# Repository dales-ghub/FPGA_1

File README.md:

A simple FPGA design using a Lattice ICE40UP5K. Does not have memory and is intended to be programmed exernally. Takes 3V3 volts on pin 40 and has regulator for 1V2.

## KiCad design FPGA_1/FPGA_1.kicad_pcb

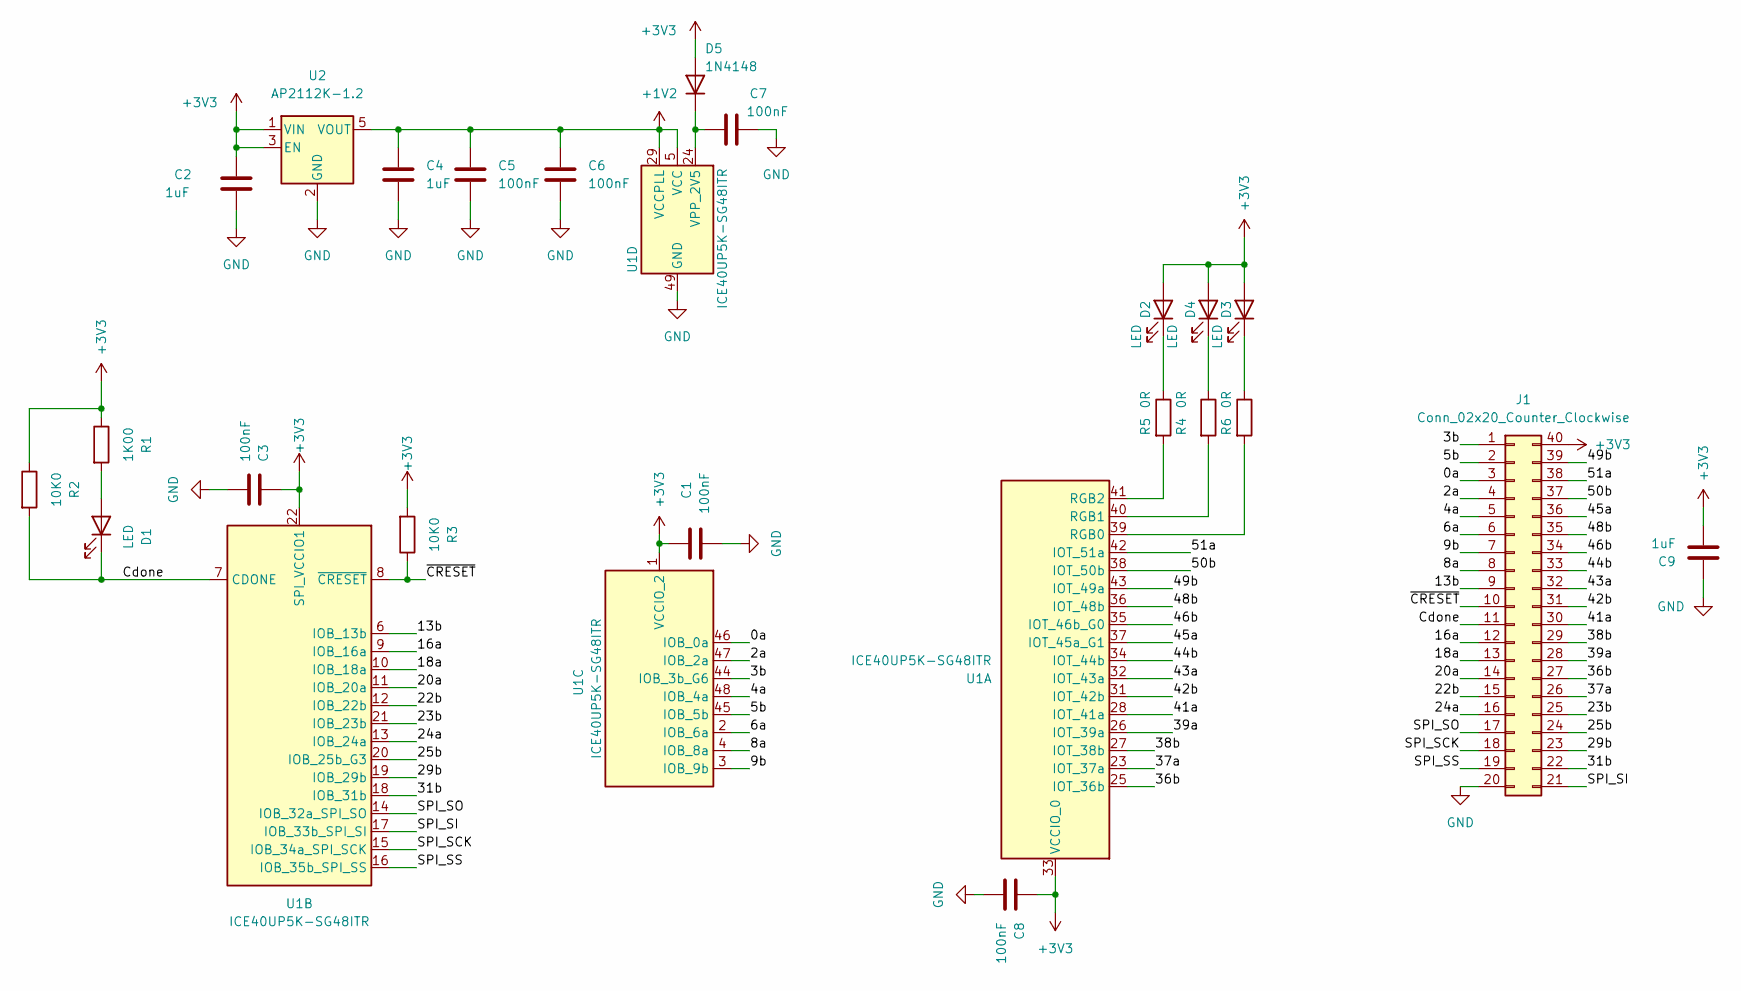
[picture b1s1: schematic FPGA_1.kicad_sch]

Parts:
C1, C3, C5, C6, C7, C8: 100nF; C_0402_1005Metric_Pad0.74x0.62mm_HandSolder
C2, C4, C9: 1uF; C_0402_1005Metric_Pad0.74x0.62mm_HandSolder
D1, D2, D3, D4: LED; LED_0603_1608Metric
D5: 1N4148; D_0402_1005Metric_Pad0.77x0.64mm_HandSolder
J1: Conn_02x20_Counter_Clockwise; DIP-40_600_ELL
R1: 1K00; R_0402_1005Metric_Pad0.72x0.64mm_HandSolder
R2, R3: 10K0; R_0402_1005Metric_Pad0.72x0.64mm_HandSolder
R4, R5, R6: 0R; R_0402_1005Metric_Pad0.72x0.64mm_HandSolder
U1: ICE40UP5K-SG48ITR; QFN-48-1EP_7x7mm_P0.5mm_EP5.6x5.6mm
U2: AP2112K-1.2; SOT-23-5

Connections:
+1V2: C4.1, C5.1, C6.1, U1.5 (VCC), U1.29 (VCCPLL), U1.30 (VCC), U2.5 (VOUT)
+3V3: C1.1, C2.1, C3.1, C8.1, C9.2, D2.2 (A), D3.2 (A), D4.2 (A), D5.2 (A), J1.40, R1.1, R2.1, R3.2, U1.1 (VCCIO_2), U1.22 (SPI_VCCIO1), U1.33 (VCCIO_0), U2.1 (VIN), U2.3 (EN)
/0a: J1.3, U1.46 (IOB_0a)
/2a: J1.4, U1.47 (IOB_2a)
/3b: J1.1, U1.44 (IOB_3b_G6)
/4a: J1.5, U1.48 (IOB_4a)
/5b: J1.2, U1.45 (IOB_5b)
/6a: J1.6, U1.2 (IOB_6a)
/8a: J1.8, U1.4 (IOB_8a)
/9b: J1.7, U1.3 (IOB_9b)
/13b: J1.9, U1.6 (IOB_13b)
/16a: J1.12, U1.9 (IOB_16a)
/18a: J1.13, U1.10 (IOB_18a)
/20a: J1.14, U1.11 (IOB_20a)
/22b: J1.15, U1.12 (IOB_22b)
/23b: J1.25, U1.21 (IOB_23b)
/24a: J1.16, U1.13 (IOB_24a)
/25b: J1.24, U1.20 (IOB_25b_G3)
/29b: J1.23, U1.19 (IOB_29b)
/31b: J1.22, U1.18 (IOB_31b)
/36b: J1.27, U1.25 (IOT_36b)
/37a: J1.26, U1.23 (IOT_37a)
/38b: J1.29, U1.27 (IOT_38b)
/39a: J1.28, U1.26 (IOT_39a)
/41a: J1.30, U1.28 (IOT_41a)
/42b: J1.31, U1.31 (IOT_42b)
/43a: J1.32, U1.32 (IOT_43a)
/44b: J1.33, U1.34 (IOT_44b)
/45a: J1.36, U1.37 (IOT_45a_G1)
/46b: J1.34, U1.35 (IOT_46b_G0)
/48b: J1.35, U1.36 (IOT_48b)
/49b: J1.39, U1.43 (IOT_49a)
/50b: J1.37, U1.38 (IOT_50b)
/51a: J1.38, U1.42 (IOT_51a)
/Cdone: D1.1 (K), J1.11, R2.2, U1.7 (CDONE)
/SPI_SCK: J1.18, U1.15 (IOB_34a_SPI_SCK)
/SPI_SI: J1.21, U1.17 (IOB_33b_SPI_SI)
/SPI_SO: J1.17, U1.14 (IOB_32a_SPI_SO)
/SPI_SS: J1.19, U1.16 (IOB_35b_SPI_SS)
/~CRESET: J1.10, R3.1, U1.8 (~CRESET)
GND: C1.2, C2.2, C3.2, C4.2, C5.2, C6.2, C7.2, C8.2, C9.1, J1.20, U1.49 (GND), U2.2 (GND)
unnamed: C7.1, D5.1 (K), U1.24 (VPP_2V5)
unnamed: D1.2 (A), R1.2
unnamed: D2.1 (K), R4.1
unnamed: D3.1 (K), R5.1
unnamed: D4.1 (K), R6.1
unnamed: R4.2, U1.41 (RGB2)
unnamed: R5.2, U1.39 (RGB0)
unnamed: R6.2, U1.40 (RGB1)

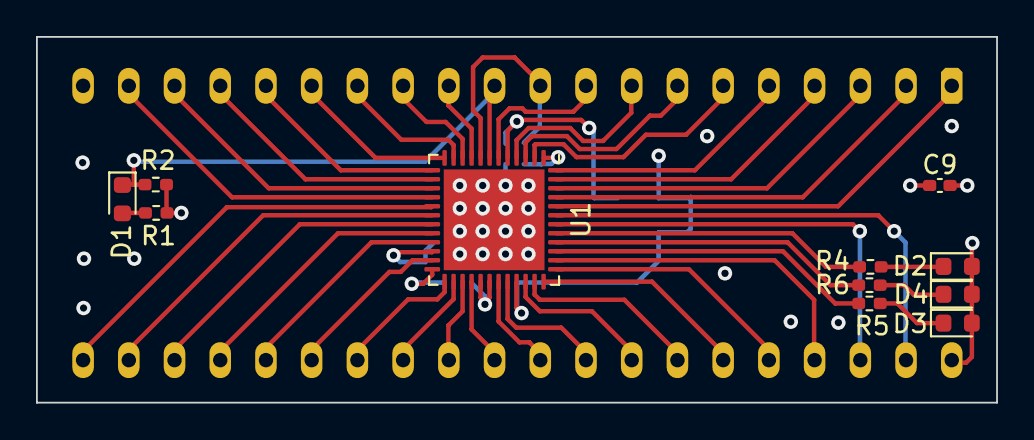
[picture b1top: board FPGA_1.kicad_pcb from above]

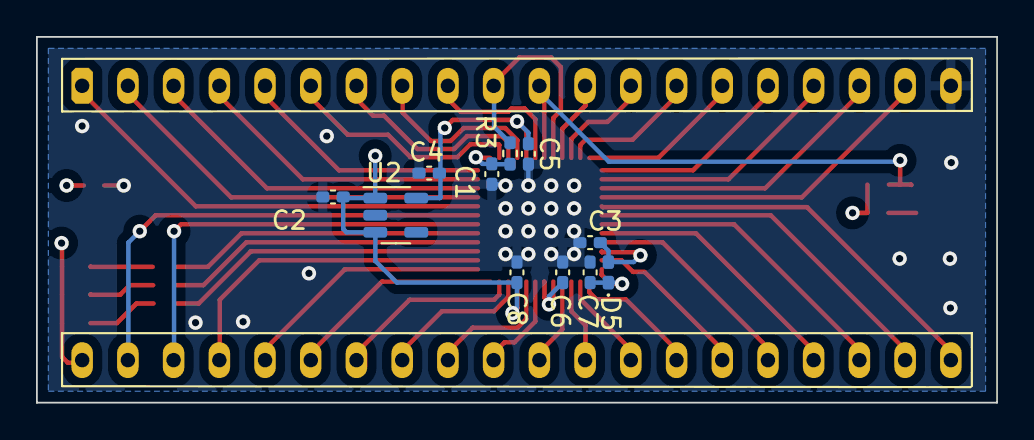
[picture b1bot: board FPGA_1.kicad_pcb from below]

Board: 4 copper layers, 53.3 x 20.3 mm, 23 parts (11 on the bottom side), 49 nets.
